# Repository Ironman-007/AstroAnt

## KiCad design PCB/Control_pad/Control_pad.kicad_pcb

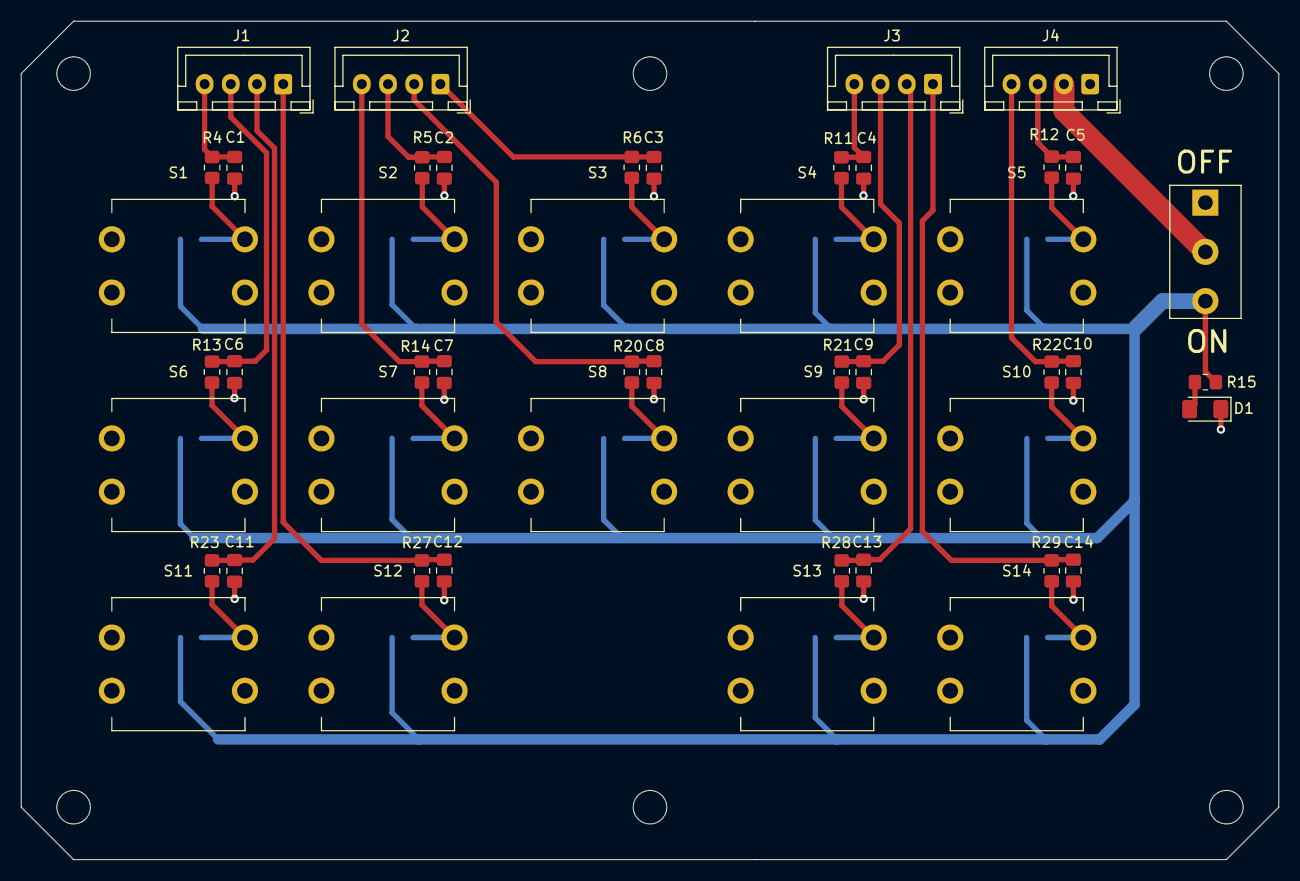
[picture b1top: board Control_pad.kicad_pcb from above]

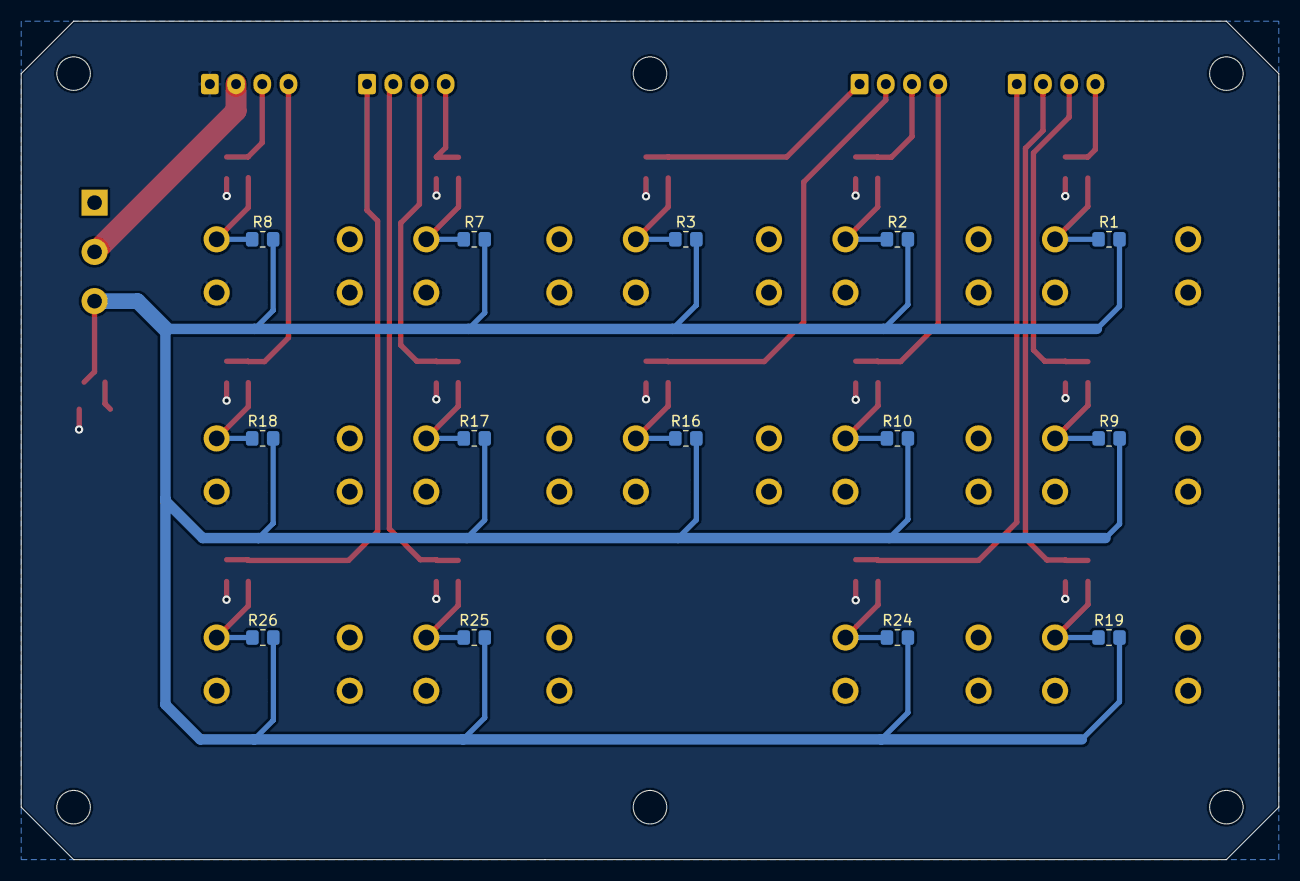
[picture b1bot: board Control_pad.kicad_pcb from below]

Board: 2 copper layers, 120.0 x 80.0 mm, 69 parts (14 on the bottom side), 32 nets.

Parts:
C1, C2, C3, C4, C5, C6, C7, C8, C9, C10, C11, C12, C13, C14: 4.7uF; C_0805_2012Metric_Pad1.18x1.45mm_HandSolder
D1: LED; LED_1206_3216Metric_Pad1.42x1.75mm_HandSolder
H1, H2, H3, H4, H5, H6: MountingHole; MountingHole_3.2mm_M3
J1, J2, J3, J4: JST_SH_4_pin_male; JST_XH_B4B-XH-A_1x04_P2.50mm_Vertical
R1, R2, R3, R4, R5, R6, R7, R8, R9, R10, R11, R12, R13, R14, R15, R16, R17, R18, R19, R20, R21, R22, R23, R24, R25, R26, R27, R28, R29: 10k; R_0805_2012Metric_Pad1.20x1.40mm_HandSolder
S1, S2, S3, S4, S5, S6, S7, S8, S9, S10, S11, S12, S13, S14: 1825910-6; TWTADE_12mmx12mm_tactile_switch
SW1: SW_SPDT; CYT1107

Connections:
+3V3: R1.2, R2.2, R3.2, R7.2, R8.2, R9.2, R10.2, R15.1, R16.2, R17.2, R18.2, R19.2, R24.2, R25.2, R26.2, SW1.3
/A0: C5.1, J4.3, R12.1
/A1: C10.1, J4.4, R22.1
/A2: C14.1, J3.1, R29.1
/A3: C13.1, J3.2, R28.1
/A4: C9.1, J3.3, R21.1
/A5: C4.1, J3.4, R11.1
/D2: C3.1, J2.1, R6.1
/D5: C8.1, J2.2, R20.1
/D6: C2.1, J2.3, R5.1
/D9: C7.1, J2.4, R14.1
/D10: C12.1, J1.1, R27.1
/D11: C11.1, J1.2, R23.1
/D12: C6.1, J1.3, R13.1
/D13: C1.1, J1.4, R4.1
GND: C1.2, C2.2, C3.2, C4.2, C5.2, C6.2, C7.2, C8.2, C9.2, C10.2, C11.2, C12.2, C13.2, C14.2, D1.1, J4.1, S1.3, S1.4, S2.3, S2.4, S3.3, S3.4, S4.3, S4.4, S5.3, S5.4, S6.3, S6.4, S7.3, S7.4, S8.3, S8.4, S9.3, S9.4, S10.3, S10.4, S11.3, S11.4, S12.3, S12.4, S13.3, S13.4, S14.3, S14.4
unnamed: D1.2, R15.2
unnamed: J4.2, SW1.2
unnamed: R1.1, R4.2, S1.2
unnamed: R2.1, R5.2, S2.2
unnamed: R3.1, R6.2, S3.2
unnamed: R10.1, R14.2, S7.2
unnamed: R7.1, R11.2, S4.2
unnamed: R8.1, R12.2, S5.2
unnamed: R9.1, R13.2, S6.2
unnamed: R16.1, R20.2, S8.2
unnamed: R17.1, R21.2, S9.2
unnamed: R18.1, R22.2, S10.2
unnamed: R19.1, R23.2, S11.2
unnamed: R24.1, R27.2, S12.2
unnamed: R25.1, R28.2, S13.2
unnamed: R26.1, R29.2, S14.2
